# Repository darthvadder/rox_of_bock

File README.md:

# rox_of_bock
Kicad, LT-Spice and BOM files for a Guitar Overdrive Pedal

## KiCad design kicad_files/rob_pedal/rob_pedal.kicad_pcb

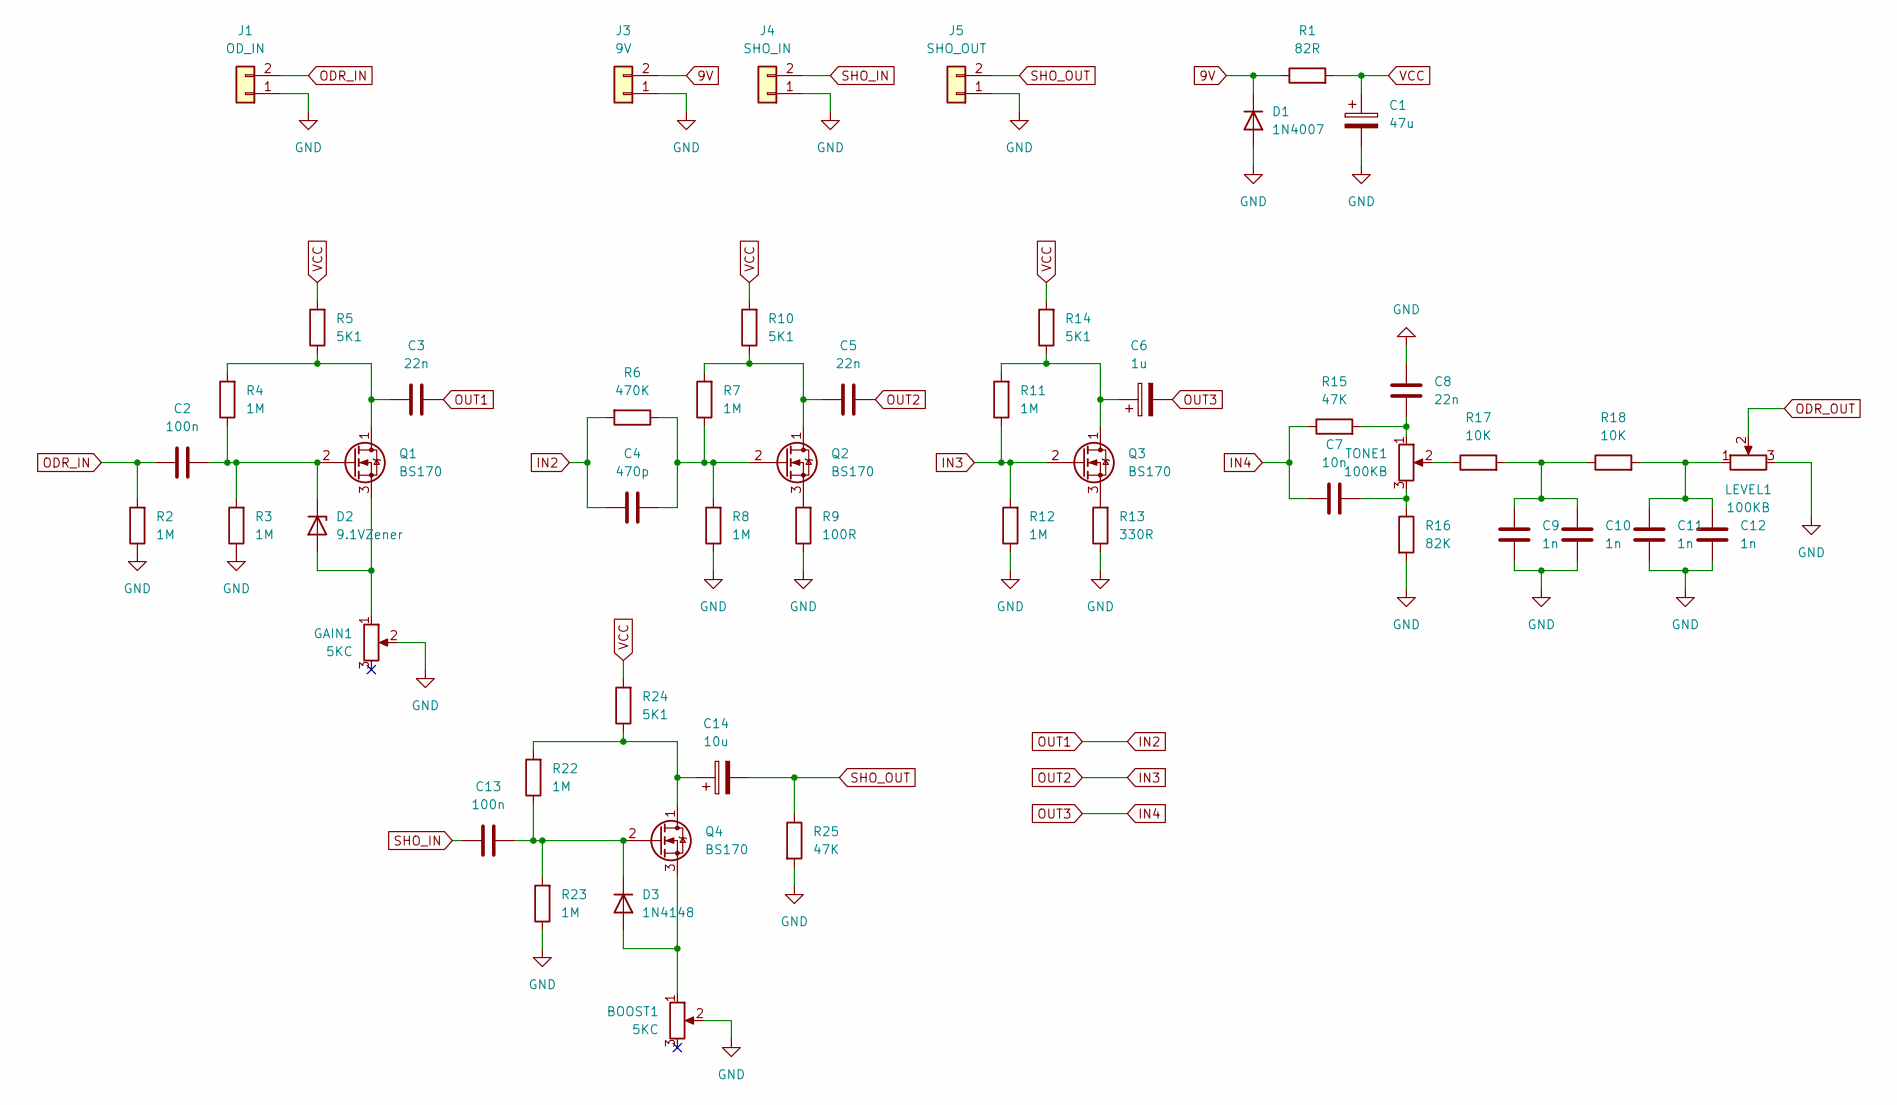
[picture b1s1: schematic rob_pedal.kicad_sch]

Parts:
BOOST1: 5KC; SolderWire-0.5sqmm_1x02_P4.6mm_D0.9mm_OD2.1mm
C1: 47u; CP_Radial_D5.0mm_P2.00mm
C2, C13: 100n; C_Rect_L13.0mm_W4.0mm_P10.00mm_FKS3_FKP3_MKS4
C3, C5, C8: 22n; C_Rect_L13.0mm_W4.0mm_P10.00mm_FKS3_FKP3_MKS4
C4: 470p; C_Rect_L7.0mm_W2.5mm_P5.00mm
C6: 1u; CP_Radial_D5.0mm_P2.50mm
C7: 10n; C_Rect_L10.0mm_W3.0mm_P7.50mm_MKS4
C9, C10, C11, C12: 1n; C_Rect_L13.0mm_W4.0mm_P10.00mm_FKS3_FKP3_MKS4
C14: 10u; CP_Radial_D6.3mm_P2.50mm
D1: 1N4007; D_DO-41_SOD81_P7.62mm_Horizontal
D2: 9.1VZener; D_DO-41_SOD81_P7.62mm_Horizontal
D3: 1N4148; D_DO-41_SOD81_P7.62mm_Horizontal
GAIN1: 5KC; SolderWire-0.5sqmm_1x02_P4.6mm_D0.9mm_OD2.1mm
J1: OD_IN; SolderWire-0.5sqmm_1x02_P4.6mm_D0.9mm_OD2.1mm
J3: 9V; SolderWire-0.5sqmm_1x02_P4.6mm_D0.9mm_OD2.1mm
J4: SHO_IN; SolderWire-0.5sqmm_1x02_P4.6mm_D0.9mm_OD2.1mm
J5: SHO_OUT; SolderWire-0.5sqmm_1x02_P4.6mm_D0.9mm_OD2.1mm
LEVEL1: 100KB; SolderWire-0.5sqmm_1x03_P4.6mm_D0.9mm_OD2.1mm
Q1, Q2, Q3, Q4: BS170; Transistor_THT_2mmRM
R1: 82R; R_Axial_DIN0207_L6.3mm_D2.5mm_P10.16mm_Horizontal
R2, R3, R4, R7, R8, R11, R12, R22, R23: 1M; R_Axial_DIN0207_L6.3mm_D2.5mm_P10.16mm_Horizontal
R5, R10, R14, R24: 5K1; R_Axial_DIN0207_L6.3mm_D2.5mm_P10.16mm_Horizontal
R6: 470K; R_Axial_DIN0207_L6.3mm_D2.5mm_P10.16mm_Horizontal
R9: 100R; R_Axial_DIN0207_L6.3mm_D2.5mm_P10.16mm_Horizontal
R13: 330R; R_Axial_DIN0207_L6.3mm_D2.5mm_P10.16mm_Horizontal
R15, R25: 47K; R_Axial_DIN0207_L6.3mm_D2.5mm_P10.16mm_Horizontal
R16: 82K; R_Axial_DIN0207_L6.3mm_D2.5mm_P10.16mm_Horizontal
R17, R18: 10K; R_Axial_DIN0207_L6.3mm_D2.5mm_P10.16mm_Horizontal
TONE1: 100KB; SolderWire-0.5sqmm_1x03_P4.6mm_D0.9mm_OD2.1mm

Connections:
9V: D1.1 (K), J3.2, R1.1
GND: BOOST1.2, C1.2, C8.2, C9.1, C10.1, C11.1, C12.1, D1.2 (A), GAIN1.2, J1.1, J3.1, J4.1, J5.1, LEVEL1.3, R2.1, R3.1, R8.1, R9.1, R12.1, R13.1, R16.2, R23.1, R25.2
IN2: C3.2, C4.1, R6.2
IN3: C5.2, Q3.2 (G), R11.1, R12.2
IN4: C6.2, C7.1, R15.1
unnamed: BOOST1.1, D3.2 (A), Q4.3 (S)
unnamed: C2.2, D2.1 (K), Q1.2 (G), R3.2, R4.1
unnamed: C3.1, Q1.1 (D), R4.2, R5.1
unnamed: C4.2, Q2.2 (G), R6.1, R7.1, R8.2
unnamed: C5.1, Q2.1 (D), R7.2, R10.1
unnamed: C6.1, Q3.1 (D), R11.2, R14.1
unnamed: C7.2, R16.1, TONE1.3
unnamed: C8.1, R15.2, TONE1.1
unnamed: C9.2, C10.2, R17.2, R18.1
unnamed: C11.2, C12.2, LEVEL1.1, R18.2
unnamed: C13.2, D3.1 (K), Q4.2 (G), R22.1, R23.2
unnamed: C14.1, Q4.1 (D), R22.2, R24.1
unnamed: D2.2 (A), GAIN1.1, Q1.3 (S)
unnamed: Q2.3 (S), R9.2
unnamed: Q3.3 (S), R13.2
unnamed: R17.1, TONE1.2
ODR_IN: C2.1, J1.2, R2.2
ODR_OUT: LEVEL1.2
SHO_IN: C13.1, J4.2
SHO_OUT: C14.2, J5.2, R25.1
VCC: C1.1, R1.2, R5.2, R10.2, R14.2, R24.2

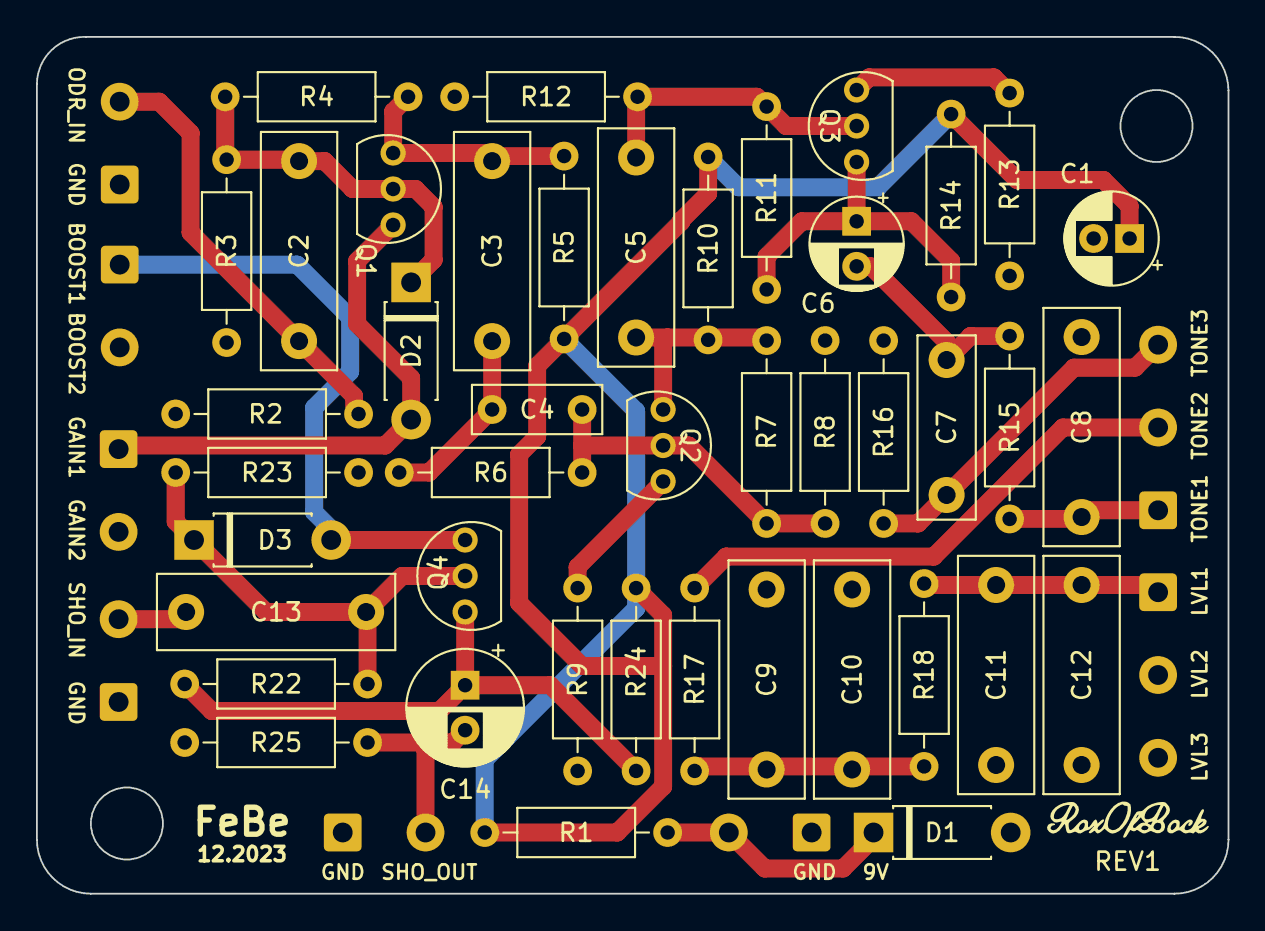
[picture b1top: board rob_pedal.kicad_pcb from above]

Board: 2 copper layers, 66.2 x 47.6 mm, 52 parts (0 on the bottom side), 25 nets.

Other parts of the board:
REV1: logo

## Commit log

2023-11-30 change readme
2023-11-30 add kicad files
2023-11-30 first placement for 125B case
2023-12-01 add spice simulation
2023-12-01 added routing
2023-12-01 added ibom
2023-12-01 added mounting holes
2023-12-02 added silkscreen and logo
